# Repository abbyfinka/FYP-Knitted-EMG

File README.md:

# Development of a Flexible EMG Readout Board for Wearable Hand Movement Prediction

* Final Year Project
* MEng Electrical and Electronic Engineering
* Imperial College London
* Supervisor: Professor Kristel Fobelets

This project aimed to design a low-cost, compact sEMG acquisition device to interface into a knitted armband, using knitted electrodes to acquire sEMG signals. The device achieves a high-sampling rate, with sufficient resolution, and robust wireless transmission with no dropped packets. An embedded classification pipeline was developed using an MLP architecture, aiming to classify six hand/wrist movements. The embedded implementation was not fully tested, however the model was validated using data collected from an alternative acquisition device, the Cyton Board. 

This repository contains all of the code developed in this project, including the PCB files of the hardware developed. 

## Repository Structure

This repo contains:
- `\Hardware`: Contains PCB design files
- `\App`: Python code to run GUI to visualise and log the signals
- `\ESP32`: C++ firmware, developed using PlatformIO, to run on ESP32 and interface with the PCB to acquire signals
  - `\ESP32\test`: Unit tests for firmware
- `\Classification`: Jupyter notebook to generate MLP model weights

## User Guide

### Visualising and Logging Data

Visualising and logging data using this device is simple to set up with little installation. The steps are detailed below.

1. Clone the project repository by running the following commands in the terminal of the desired file location.

   `git clone https://github.com/abbyfinka/FYP-Knitted-EMG`

   `cd FYP-Knitted-EMG/App`

3. Run the Python script `EMGApp.py`. A GUI will open showing live data. An indicator light on the device will turn on when the device has successfully connected.

4. Logs can be found at `FYP-Knitted-EMG/App/Logs/[TIMESTAMP]_emg_log.txt`

If data is not visible, check the terminal. If there are any issues connecting to the ESP32, first check that there are no other Bluetooth devices connected to your device. If the issue persists check that the ESP32 is turned on and in range, this can be verified using an app such as nRF Connect.

To use the device for acquiring signals other than sEMG, the Python GUI can be configured by minor changes to the source code. `logging` can be set to `False` to disable logging received data to a text file, setting `filtering` to `True` will enable real time band pass filtering of the signal, with cutoff frequencies determined by `fc_lowpass` and `fc_highpass`. Additionally, adjusting `ylim_time`, `ylim_freq` and `PRINT_INTERVAL` can adjust the initial axis of the time and frequency plots.

### Updating Embedded Classification Model

The AIfES can easily be updated with new weights, the steps required are detailed below.

1. Clone the project repository by running the following commands in the terminal of the desired file location.

   `git clone https://github.com/abbyfinka/FYP-Knitted-EMG`

   `cd FYP-Knitted-EMG/Classification`

3. Setup EMGPromptApp, accessible [here](https://github.com/LilOz/EMGPromptApp), developed by Ayman Osman, to collect training data. User instructions can be found in the repository README.

    Update line 318 of `main.py`, to account for the increased sampling rate. 
    
    Corrected line: `time_step = 0.001`

4. Collect data with this application. Run the developed Python GUI instead of the OpenBCI software.

5. Upload training data and run `MLP-Training-for-ESP32.ipynb`. The last cell will print a string that can be copied into `FYP-Knitted-EMG/ESP32/lib/Weights/weights.h`

6. Upload the new firmware to the ESP32. Classification output is available over BLE in the GUI.

### Using the Device

Firmware for signal acquisition is already uploaded to the device, for any changes, connect the programming PCB to upload new code.

1. Connect LiPo battery to switch on device, red LED will turn on to indicate power.
   
2. Click the RESET button to start the code. Blue LED should flash on and off. If the blue LED stays on, the ADS1198 has not been initialised correctly, press RESET again.
   
3. Connect to the device as described above, blue LED will turn on to indicate BLE connection

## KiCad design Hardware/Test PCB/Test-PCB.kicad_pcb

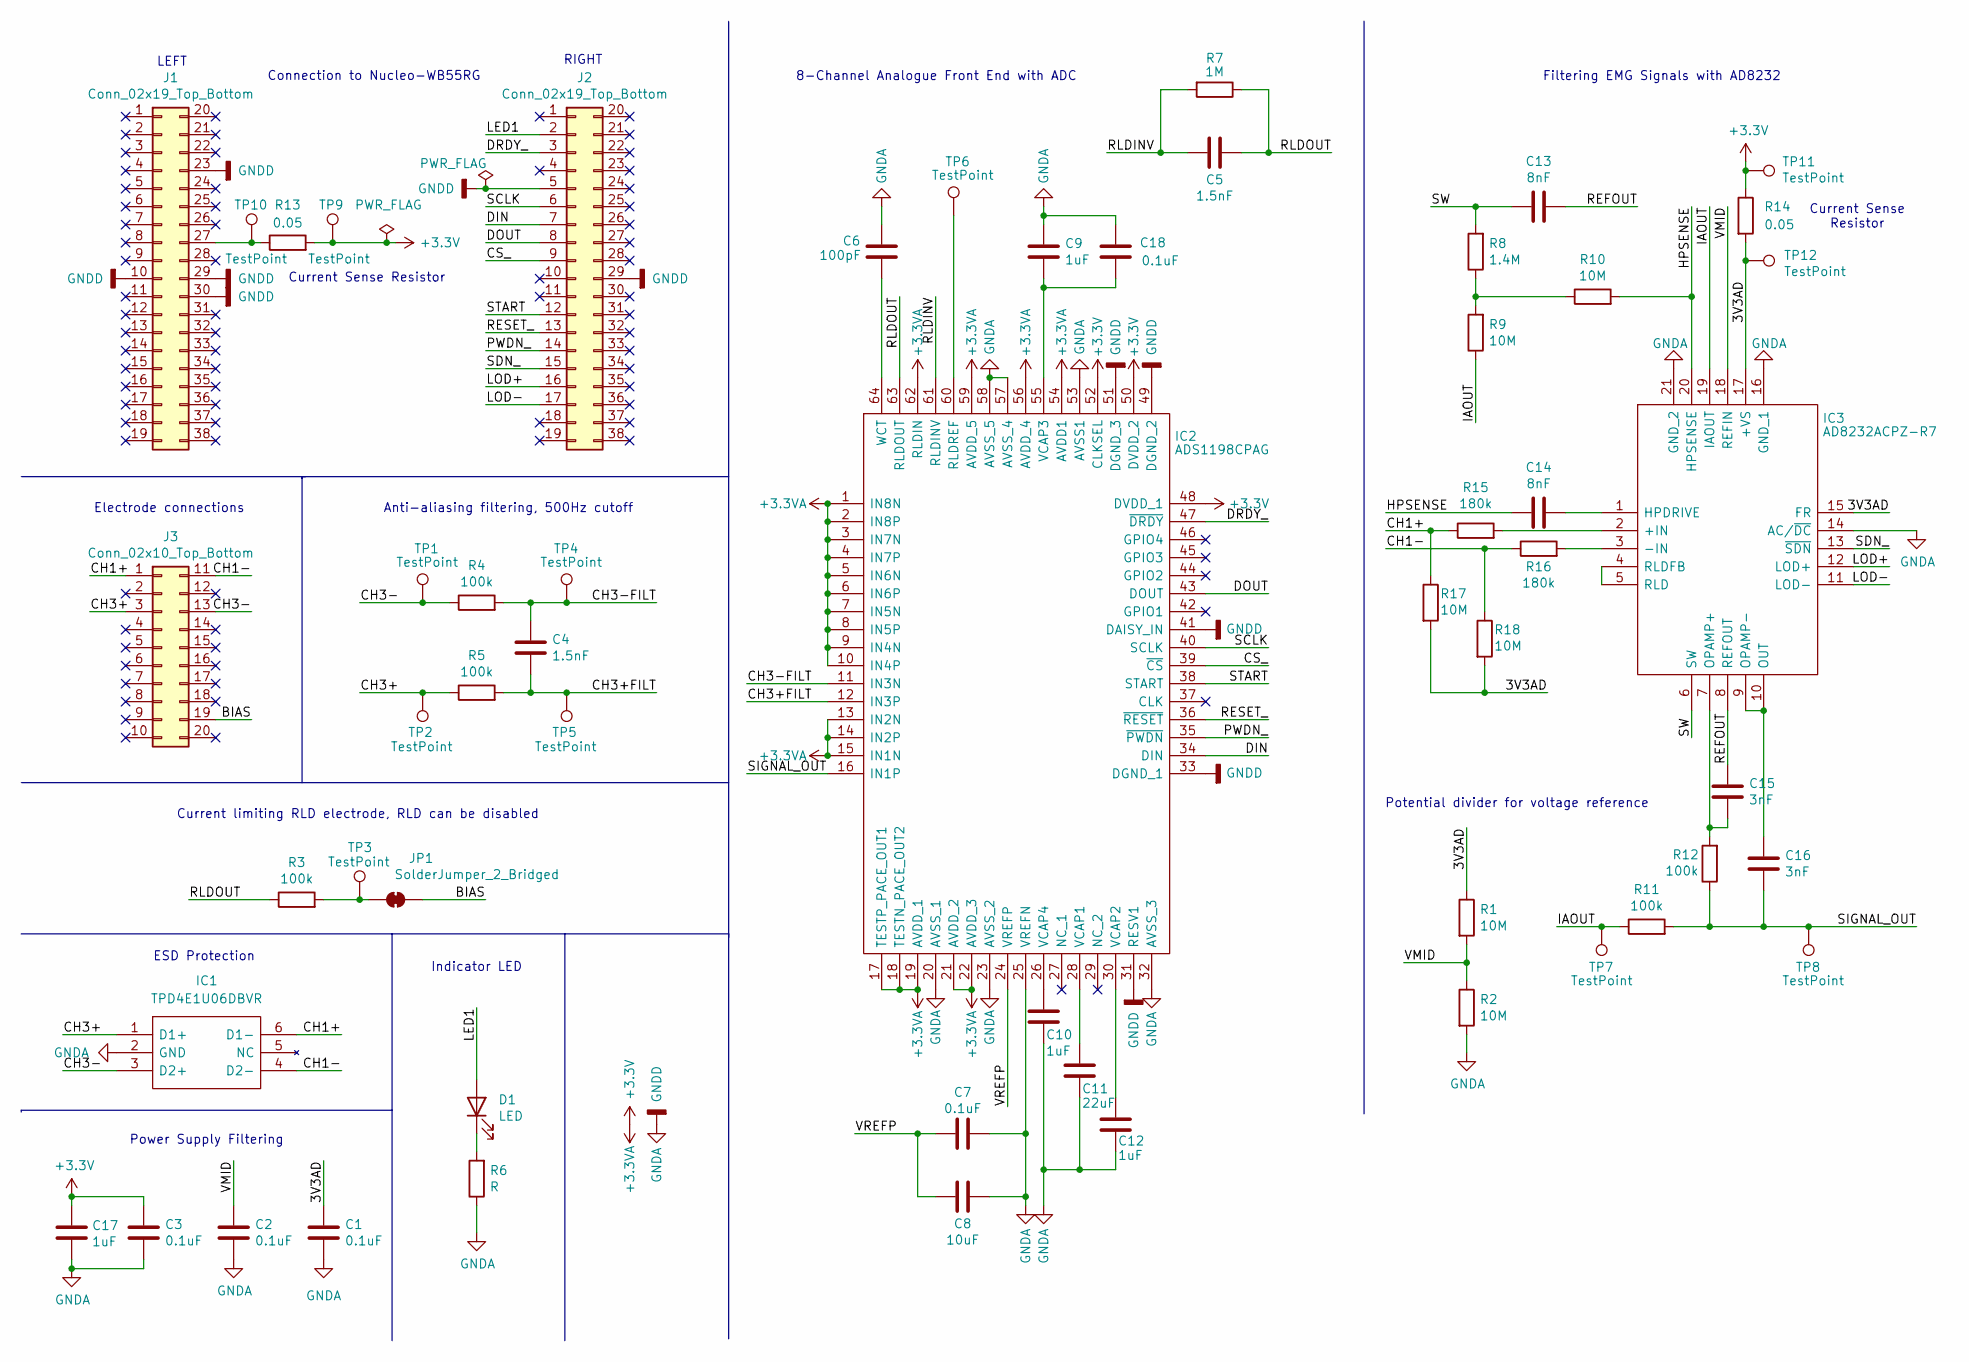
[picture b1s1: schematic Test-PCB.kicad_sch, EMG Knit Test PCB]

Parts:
C1, C2, C3, C7, C18: 0.1uF; C_0805_2012Metric
C4, C5: 1.5nF; C_0805_2012Metric
C6: 100pF; C_0805_2012Metric
C8: 10uF; C_0805_2012Metric
C9, C10, C12, C17: 1uF; C_0805_2012Metric
C11: 22uF; C_0805_2012Metric
C13, C14: 8nF; C_0805_2012Metric
C15, C16: 3nF; C_0805_2012Metric
D1: LED; LED_0805_2012Metric
IC1: TPD4E1U06DBVR; SOT95P280X145-6N; Manufacturer_Part_Number TPD4E1U06DBVR
IC2: ADS1198CPAG; QFP50P1200X1200X120-64N; Mouser Part Number 595-ADS1198CPAG
IC3: AD8232ACPZ-R7; QFN50P400X400X80-21N-D; Manufacturer_Part_Number AD8232ACPZ-R7; Mouser Part Number 584-AD8232ACPZ-R7
J1, J2: Conn_02x19_Top_Bottom; PinHeader_2x19_P2.54mm_Vertical_Top_Bottom
J3: Conn_02x10_Top_Bottom; PinHeader_2x10_P2.54mm_Horizontal_Top_Bottom
JP1: SolderJumper_2_Bridged; SolderJumper-2_P1.3mm_Bridged_RoundedPad1.0x1.5mm
R1, R2, R9, R10, R17, R18: 10M; R_0805_2012Metric
R3, R4, R5, R11, R12: 100k; R_0805_2012Metric
R6: R; R_0805_2012Metric
R7: 1M; R_0805_2012Metric
R8: 1.4M; R_0805_2012Metric
R13, R14: 0.05; R_0805_2012Metric
R15, R16: 180k; R_0805_2012Metric
TP1, TP2, TP3, TP4, TP5, TP6, TP7, TP8, TP9, TP10, TP11, TP12: TestPoint; TestPoint_Pad_D2.0mm

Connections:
+3.3V: C3.1, C17.1, IC2.1 (IN8N), IC2.2 (IN8P), IC2.3 (IN7N), IC2.4 (IN7P), IC2.5 (IN6N), IC2.6 (IN6P), IC2.7 (IN5N), IC2.8 (IN5P), IC2.9 (IN4N), IC2.10 (IN4P), IC2.13 (IN2N), IC2.14 (IN2P), IC2.15 (IN1N), IC2.17 (TESTP_PACE_OUT1), IC2.18 (TESTN_PACE_OUT2), IC2.19 (AVDD_1), IC2.21 (AVDD_2), IC2.22 (AVDD_3), IC2.48 (DVDD_1), IC2.50 (DVDD_2), IC2.52 (CLKSEL), IC2.54 (AVDD1), IC2.56 (AVDD_4), IC2.59 (AVDD_5), IC2.62 (RLDIN), R13.2, R14.1, TP9.1, TP11.1
/3V3AD: C1.1, IC3.15 (FR), IC3.17 (+VS), R1.1, R14.2, R17.2, R18.2, TP12.1
/BIAS: J3.19, JP1.2 (B)
/CH1+: IC1.6 (D1-), J3.1, R15.1, R17.1
/CH1-: IC1.4 (D2-), J3.11, R16.1, R18.1
/CH3+: IC1.1 (D1+), J3.3, R5.1, TP2.1
/CH3+FILT: C4.2, IC2.12 (IN3P), R5.2, TP5.1
/CH3-: IC1.3 (D2+), J3.13, R4.1, TP1.1
/CH3-FILT: C4.1, IC2.11 (IN3N), R4.2, TP4.1
/CS_: IC2.39 (~CS), J2.9
/DIN: IC2.34 (DIN), J2.7
/DOUT: IC2.43 (DOUT), J2.8
/DRDY_: IC2.47 (~DRDY), J2.3
/HPSENSE: C14.2, IC3.20 (HPSENSE), R10.2
/IAOUT: IC3.19 (IAOUT), R9.1, R11.1, TP7.1
/LED1: D1.2 (A), J2.2
/LOD+: IC3.12 (LOD+), J2.16
/LOD-: IC3.11 (LOD-), J2.17
/PWDN_: IC2.35 (~PWDN), J2.14
/REFOUT: C13.1, C15.2, IC3.8 (REFOUT)
/RESET_: IC2.36 (~RESET), J2.13
/RLDINV: C5.2, IC2.61 (RLDINV), R7.2
/RLDOUT: C5.1, IC2.63 (RLDOUT), R3.1, R7.1
/SCLK: IC2.40 (SCLK), J2.6
/SDN_: IC3.13 (~SDN), J2.15
/SIGNAL_OUT: C16.1, IC2.16 (IN1P), R11.2, R12.1, TP8.1
/START: IC2.38 (START), J2.12
/SW: C13.2, IC3.6 (SW), R8.2
/VMID: C2.1, IC3.18 (REFIN), R1.2, R2.1
/VREFP: C7.1, C8.1, IC2.24 (VREFP)
GNDA: C1.2, C2.2, C3.2, C6.1, C7.2, C8.2, C9.1, C10.2, C11.2, C12.2, C17.2, C18.1, IC1.2 (GND), IC2.20 (AVSS_1), IC2.23 (AVSS_2), IC2.25 (VREFN), IC2.31 (RESV1), IC2.32 (AVSS_3), IC2.33 (DGND_1), IC2.41 (DAISY_IN), IC2.49 (DGND_2), IC2.51 (DGND_3), IC2.53 (AVSS1), IC2.57 (AVSS_4), IC2.58 (AVSS_5), IC3.14 (AC/~DC), IC3.16 (GND_1), IC3.21 (GND_2), J1.10, J1.23, J1.29, J1.30, J2.5, J2.29, R2.2, R6.1
unnamed: D1.1 (K), R6.2
unnamed: IC2.60 (RLDREF), TP6.1
unnamed: C11.1, IC2.28 (VCAP1)
unnamed: C12.1, IC2.30 (VCAP2)
unnamed: C9.2, C18.2, IC2.55 (VCAP3)
unnamed: C10.1, IC2.26 (VCAP4)
unnamed: C6.2, IC2.64 (WCT)
unnamed: IC3.2 (+IN), R15.2
unnamed: IC3.3 (-IN), R16.2
unnamed: C14.1, IC3.1 (HPDRIVE)
unnamed: C15.1, IC3.7 (OPAMP+), R12.2
unnamed: C16.2, IC3.9 (OPAMP-), IC3.10 (OUT)
unnamed: IC3.4 (RLDFB), IC3.5 (RLD)
unnamed: J1.27, R13.1, TP10.1
unnamed: JP1.1 (A), R3.2, TP3.1
unnamed: R8.1, R9.2, R10.1

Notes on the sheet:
RIGHT
Current limiting RLD electrode, RLD can be disabled
Potential divider for voltage reference
Current Sense Resistor
Electrode connections
Indicator LED
LEFT
Connection to Nucleo-WB55RG
Anti-aliasing filtering, 500Hz cutoff
Current Sense Resistor
ESD Protection
Filtering EMG Signals with AD8232
Power Supply Filtering
8-Channel Analogue Front End with ADC

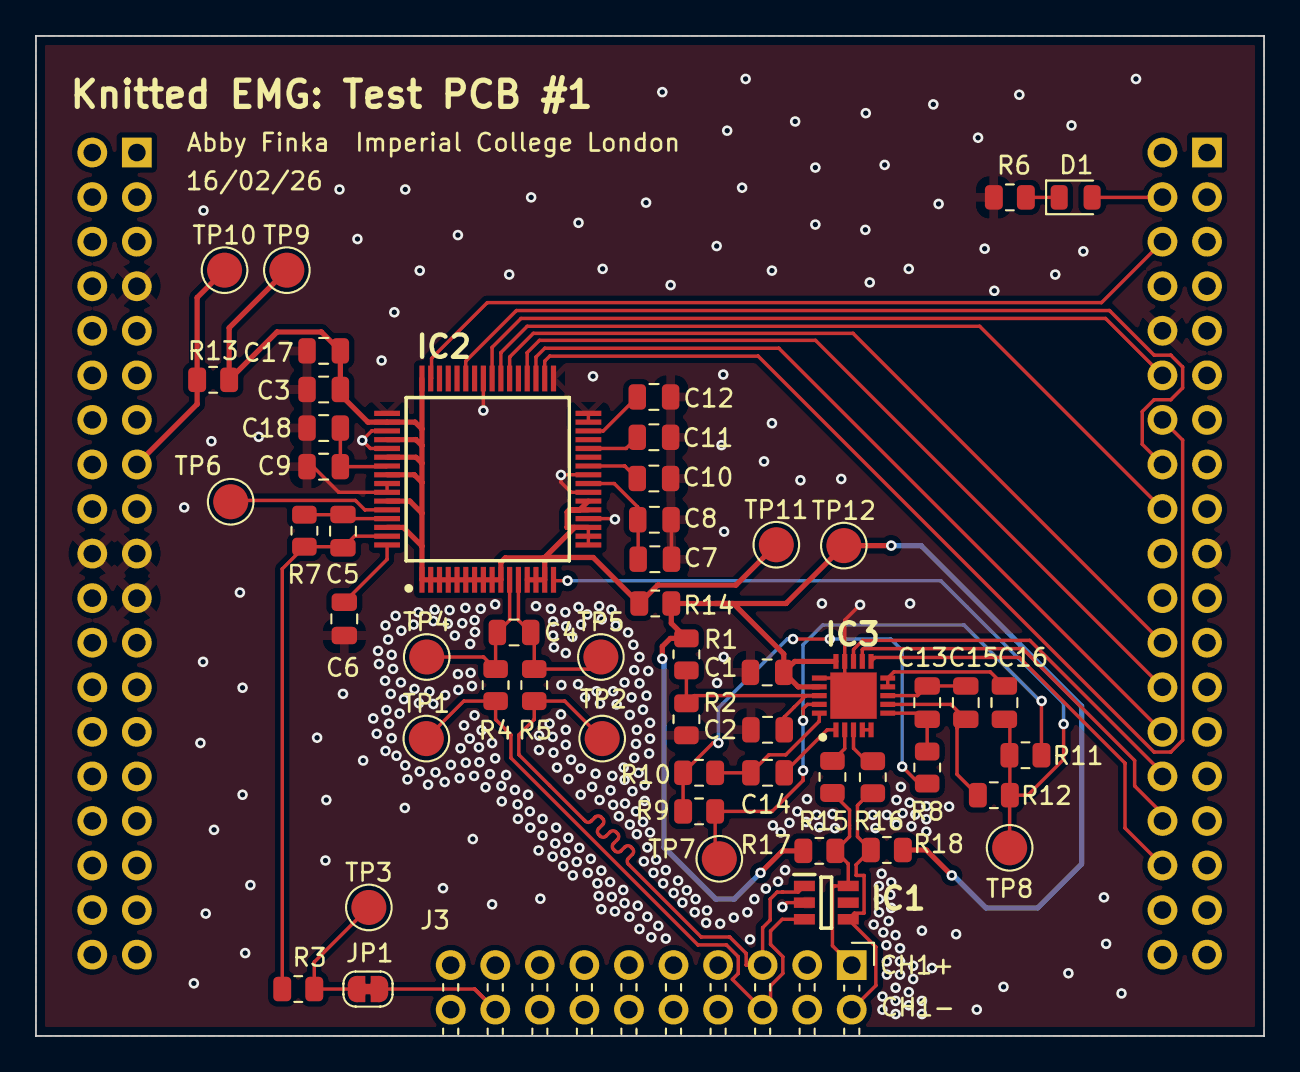
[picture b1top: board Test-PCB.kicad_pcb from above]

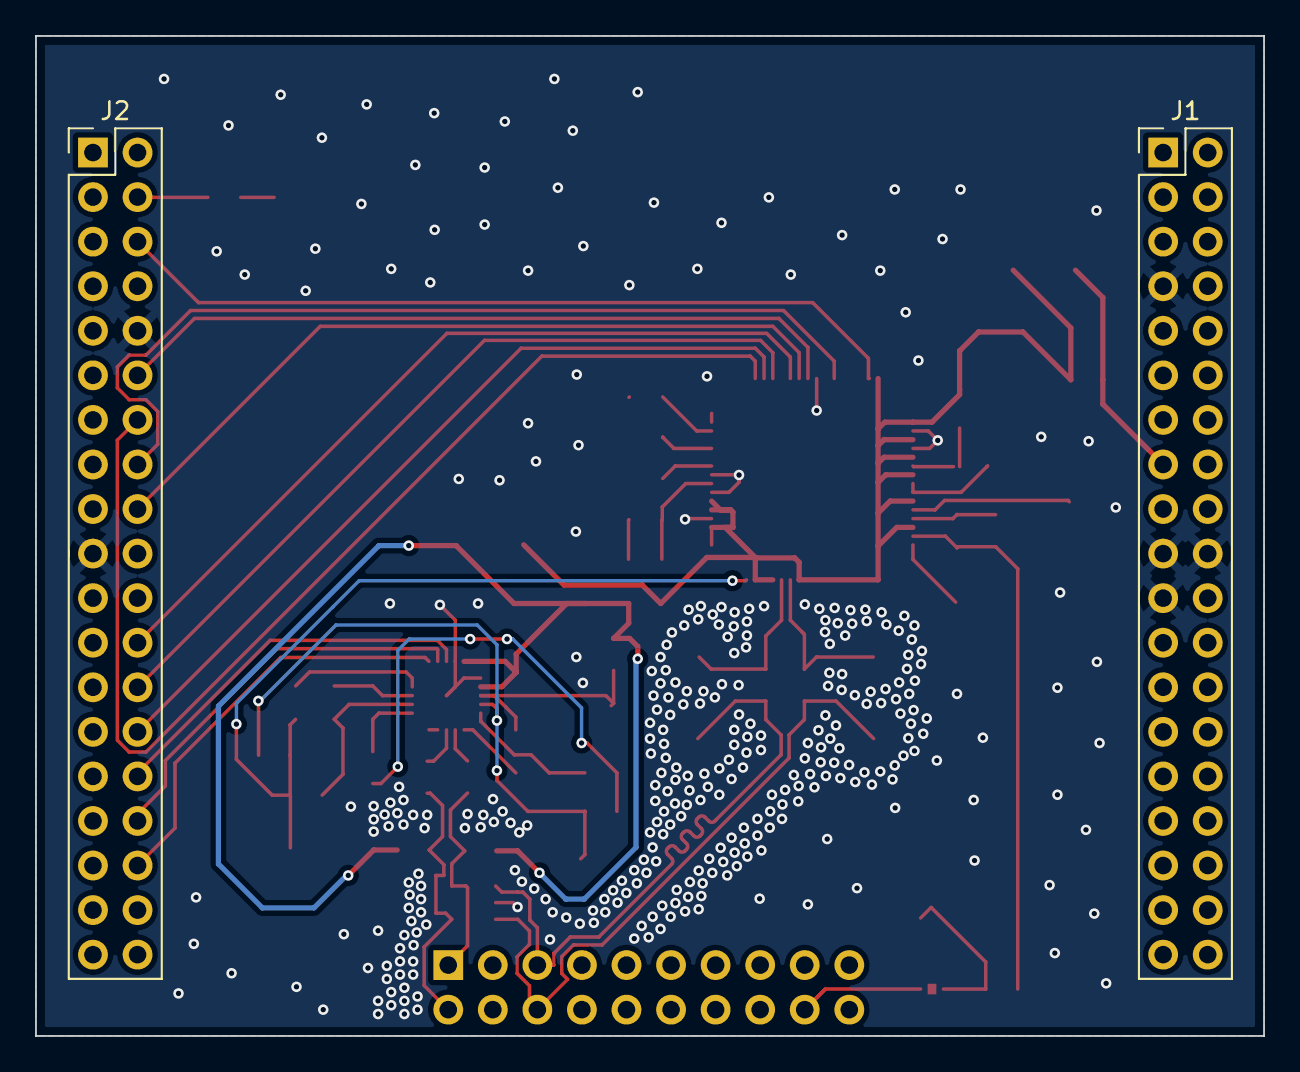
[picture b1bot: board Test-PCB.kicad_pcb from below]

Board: 2 copper layers, 70.0 x 57.0 mm, 56 parts (2 on the bottom side), 47 nets.

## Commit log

2026-03-10 Add EMGData struct
2026-03-10 SPI over hardware interrupt
2026-03-10 SPI over task notifications
2026-03-11 ring buffer
2026-04-10 general debugging
2026-04-12 add test mode
2026-04-12 move scaling to python
2026-04-19 move readChannels and batch send
2026-04-19 changed logging to match cyton
2026-04-21 bin file changes
2026-04-21 update gitignore
2026-04-27 1000Hz sampling, notch not working, bandpass filtering in python
2026-04-29 gain normalisation, notch filter not completely working
2026-04-29 Update project title in README
2026-04-29 Add project details and user guide section to README
2026-04-29 Fix typo in project title in README.md
2026-05-20 Upate .gitignore
2026-05-20 Added more DSP
2026-05-22 add feature extraction
2026-05-23 start classification (untested)
2026-05-23 add unit tests
2026-05-23 update emgApp
2026-05-25 add offset correction
2026-05-25 more classification
2026-05-25 use arduino filters for ema
2026-05-25 eight filters
2026-05-26 update EMA filter
2026-06-05 various classification updates
2026-06-06 feature extraction unit test
2026-06-06 correct logging scaling
2026-06-08 readme typo
2026-06-08 add majority voting unit test
2026-06-12 update rld and logs format
2026-06-12 build files
2026-06-12 stop tracking matlab
2026-06-12 stop tracking logs
2026-06-12 Add hardware and classification files
2026-06-12 remove big code outputs
2026-06-12 remove big code outputs again
2026-06-12 fix link
2026-06-12 fix typo
2026-06-18 add data replay
2026-06-21 Add device guide
2026-06-21 fix spacing
2026-06-21 rephrasing
2026-06-22 changes for esp on pcb
2026-06-22 updating weights
